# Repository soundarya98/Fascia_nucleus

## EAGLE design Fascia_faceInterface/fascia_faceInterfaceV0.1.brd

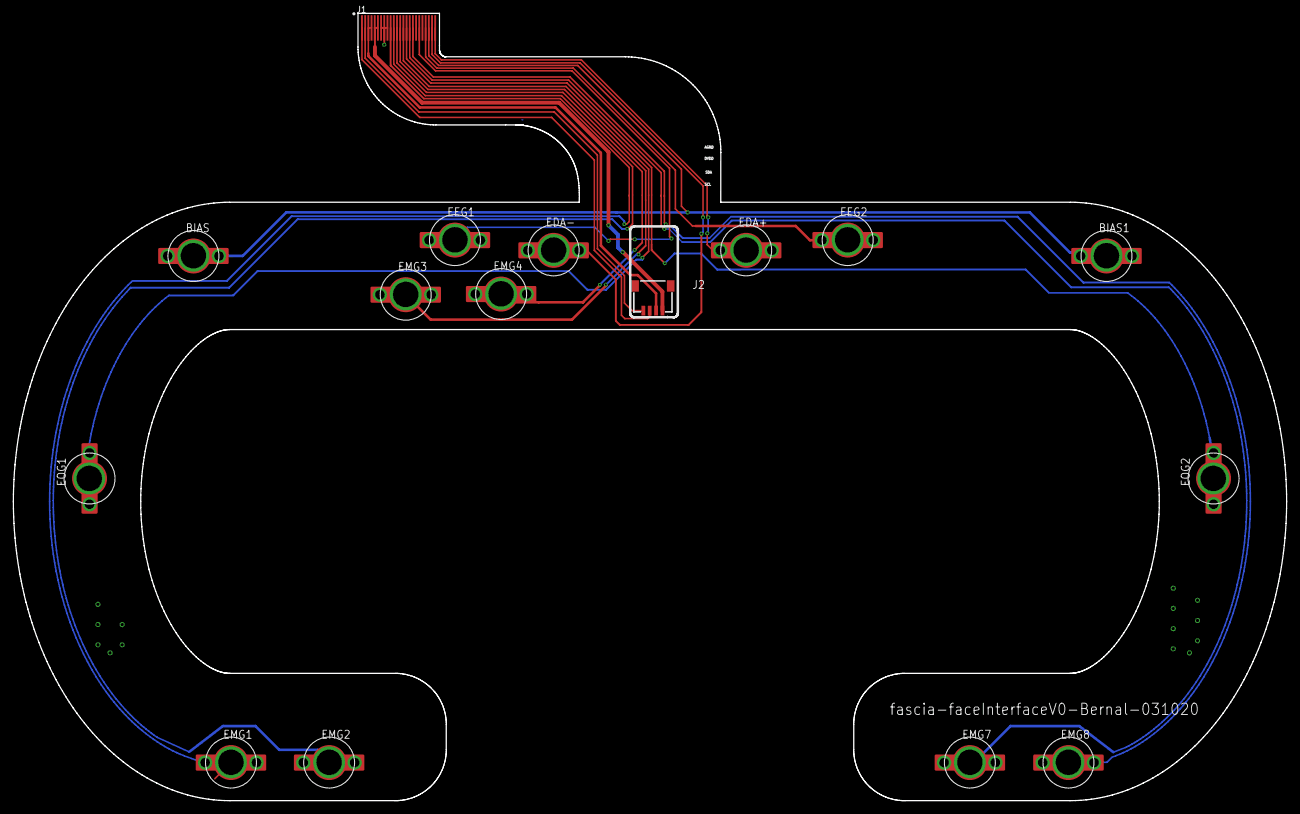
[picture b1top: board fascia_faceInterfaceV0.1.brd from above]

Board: 2 copper layers, 200.0 x 123.7 mm, 16 parts (0 on the bottom side), 18 nets.

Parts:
BIAS, BIAS1: ELECTRODE-8MMELECTRODE_8MM; ELECTRODE_V2
EDA+: ELECTRODE-8MMELECTRODE_8MM; ELECTRODE_V2
EDA-: ELECTRODE-8MMELECTRODE_8MM; ELECTRODE_V2
EEG1, EEG2: ELECTRODE-8MMELECTRODE_8MM; ELECTRODE_V2
EMG1, EMG2, EMG3, EMG4, EMG7, EMG8: ELECTRODE-8MMELECTRODE_8MM; ELECTRODE_V2
EOG1, EOG2: ELECTRODE-8MMELECTRODE_8MM; ELECTRODE_V2
J1: MOLEX_52437-247_FLEX; MOLEX_52437-2471_FLEX
J2: SM04B-SRSS-TB(LF)(SN); SM04B-SRSS-TB(LFSN)

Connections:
1N: EMG2.,, EMG2.., EMG2.P$1, EMG2.P$2, EMG2.P$3, EMG2.P$4, J1.11
1P: EMG1.,, EMG1.., EMG1.P$1, EMG1.P$2, EMG1.P$3, EMG1.P$4, J1.10
2N: EMG3.,, EMG3.., EMG3.P$1, EMG3.P$2, EMG3.P$3, EMG3.P$4, J1.13
2P: EMG4.,, EMG4.., EMG4.P$1, EMG4.P$2, EMG4.P$3, EMG4.P$4, J1.12
3N: EOG2.,, EOG2.., EOG2.P$1, EOG2.P$2, EOG2.P$3, EOG2.P$4, J1.15
3P: EOG1.,, EOG1.., EOG1.P$1, EOG1.P$2, EOG1.P$3, EOG1.P$4, J1.14
4N: EMG8.,, EMG8.., EMG8.P$1, EMG8.P$2, EMG8.P$3, EMG8.P$4, J1.17
4P: EMG7.,, EMG7.., EMG7.P$1, EMG7.P$2, EMG7.P$3, EMG7.P$4, J1.16
5N: EEG1.,, EEG1.., EEG1.P$1, EEG1.P$2, EEG1.P$3, EEG1.P$4, J1.19
6N: EEG2.,, EEG2.., EEG2.P$1, EEG2.P$2, EEG2.P$3, EEG2.P$4, J1.21
AGND: J1.7, J1.8, J1.9
BIAS: BIAS.,, BIAS.., BIAS.P$1, BIAS.P$2, BIAS.P$3, BIAS.P$4, BIAS1.,, BIAS1.., BIAS1.P$1, BIAS1.P$2, BIAS1.P$3, BIAS1.P$4, J1.22
DVDD: J1.3, J1.4, J2.2
EDA+: EDA+.,, EDA+.., EDA+.P$1, EDA+.P$2, EDA+.P$3, EDA+.P$4, J1.24
EDA-: EDA-.,, EDA-.., EDA-.P$1, EDA-.P$2, EDA-.P$3, EDA-.P$4, J1.23
GND: J1.5, J1.6, J2.1
S0_I2C_SCL: J1.2, J2.4
S0_I2C_SDA: J1.1, J2.3
